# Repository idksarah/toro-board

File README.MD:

# toro-board
fully custom gasket mount 60% hot swappable alice keyboard using a raspberry pi pico. <br>

<br>
made this bc alice keyboards r cool but i've already spent too much on keyboards.

## firmware
qmk firmware

## bom

| item                                                                                     | quantity | price  | description              | vendor     | link                                                                                                                   |
|------------------------------------------------------------------------------------------|----------|--------|--------------------------|------------|------------------------------------------------------------------------------------------------------------------------|
| plate                                                                                    | 1 pc     | 3.44   | 3d-printed acrylic plate            | jlccnc     | —                                                                                                                      |
| pcb                                                                                      | 5 pc     | 21.60  | pcb                      | jlcpcb     | —                                                                                                                      |
| case bottom                                                                              | 1 pc     | 28.34  | 3d-printed acrylic bottom case              | jlccnc     | —                                                                                                                      |
| case top                                                                                 | 1 pc     | 9.35   | 3d-printed acrylic top case                 | jlccnc     | —                                                                                                                      |
| [163 keys british racing green keyboard keycaps](https://www.aliexpress.us/item/3256807785511869.html) | 163 pc   | 16.66  | keycaps                  | aliexpress | [link](https://www.aliexpress.us/item/3256807785511869.html)                                                           |
| [gateron ef curry switch 50g 5pin smd mx switch](https://www.aliexpress.us/item/3256805933064484.html) | 70 pc    | 26.69   | ef curry switches        | aliexpress | [link](https://www.aliexpress.us/item/3256805933064484.html)                                                           |
| [coiled keyboard cable type c to usb-a](https://www.aliexpress.us/item/3256808312113111.html) | 1 pc     | 7.00   | usb c to usb a cable     | aliexpress | [link](https://www.aliexpress.us/item/3256808312113111.html)                                                           |
| [70pcs kailh hot-swappable pcb socket hot plug](https://www.aliexpress.us/item/3256807039037559.html) | 70 pc    | 3.73   | kailh hot swap sockets   | aliexpress | [link](https://www.aliexpress.us/item/3256807039037559.html)                                                           |
| [15pcs gasket cotton strip](https://www.aliexpress.us/item/3256804985438216.html)        | 15 pc    | 3.74   | gasket for gasket mount  | aliexpress | [link](https://www.aliexpress.us/item/3256804985438216.html)                                                           |
| [switch puller tool](https://www.aliexpress.us/item/3256808571143767.html)               | —        | 3.92   | switch puller            | aliexpress | [link](https://www.aliexpress.us/item/3256808571143767.html)                                                           |
| shipping (jlcpcb)                                                                        | —        | 20.00  |                          | jlcpcb     | —                                                                                                                      |

---

### subtotals

- **jlcpcb total**: 21.60 (pcb) + 20.00 (shipping) → **$41.60**
- **aliexpress total**: 16.66 + 26.69 + 7.00 + 3.73 + 3.74 + 3.92 → **$61.74**
- **jlccnc total**: 3.44 + 28.34 + 9.35 → **$41.13**

---

### total: **$116.61**

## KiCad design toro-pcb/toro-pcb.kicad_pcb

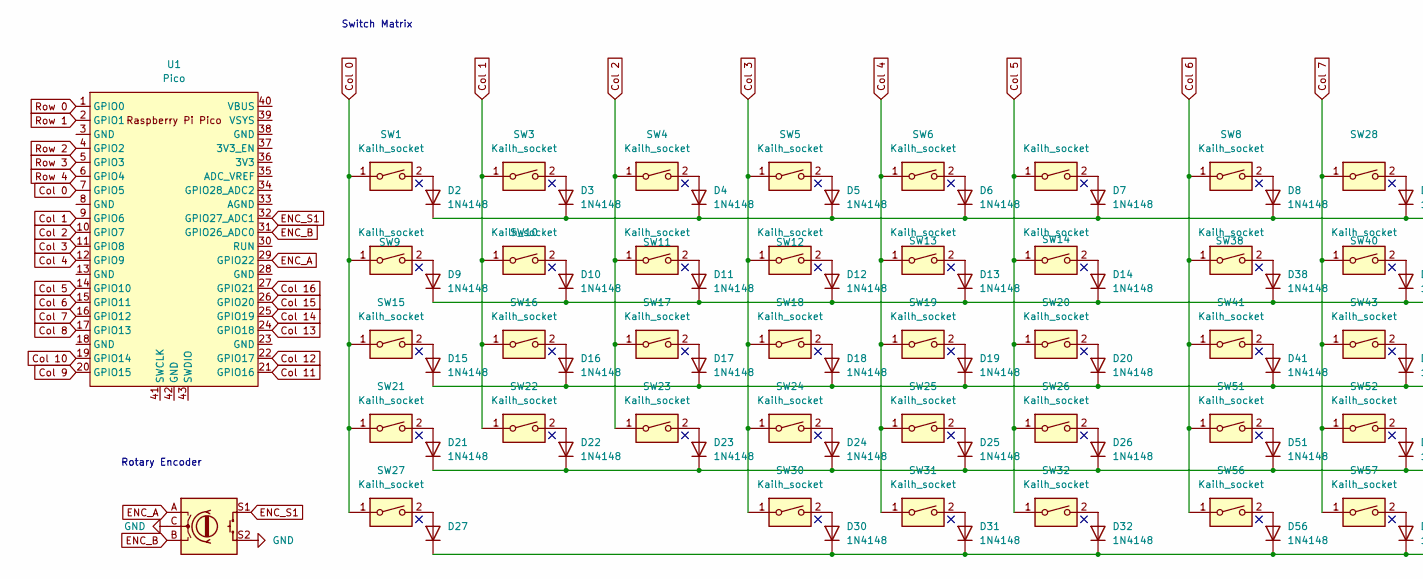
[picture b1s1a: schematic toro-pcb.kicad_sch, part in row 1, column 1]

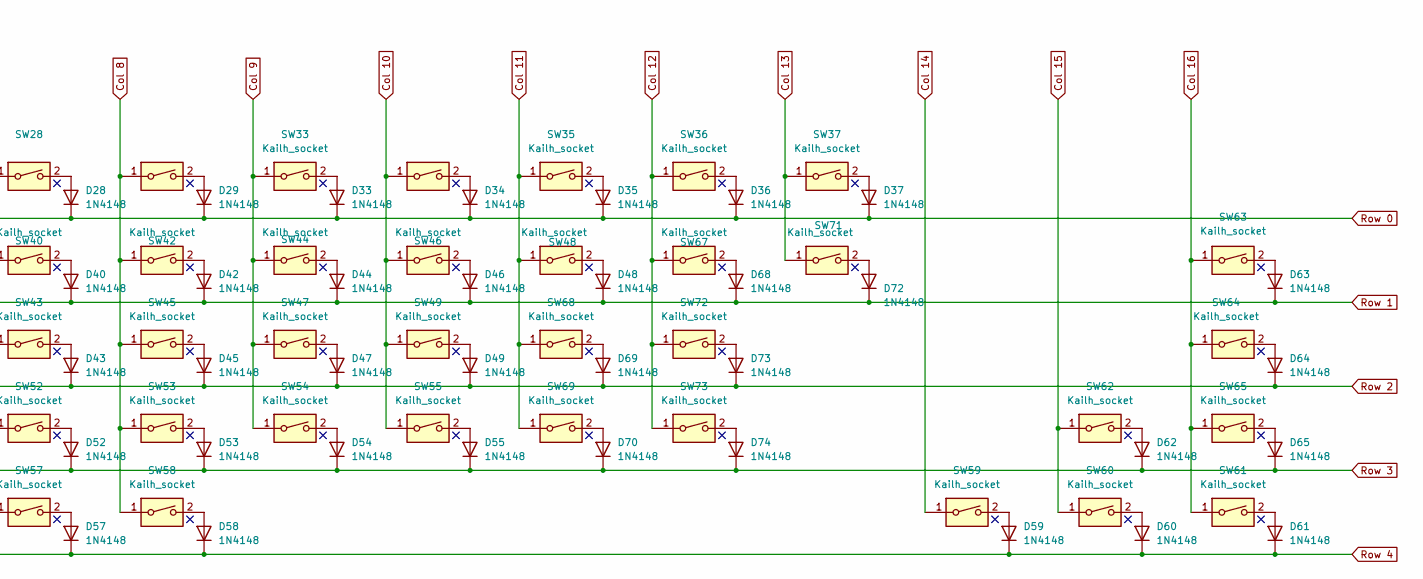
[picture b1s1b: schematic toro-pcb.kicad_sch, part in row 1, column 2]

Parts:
D2, D3, D4, D5, D6, D7, D8, D9, D10, D11, D12, D13, D14, D15, D16, D17, D18, D19, D20, D21, D22, D23, D24, D25, D26, D27, D28, D29, D30, D31, D32, D33, D34, D35, D36, D37, D38, D40, D41, D42, D43, D44, D45, D46, D47, D48, D49, D51, D52, D53, D54, D55, D56, D57, D58, D59, D60, D61, D62, D63, D64, D65, D68, D69, D70, D72, D73, D74: 1N4148; D_DO-35_SOD27_P7.62mm_Horizontal
SW1, SW3, SW4, SW5, SW6, SW7, SW8, SW9, SW10, SW11, SW12, SW13, SW14, SW15, SW16, SW17, SW18, SW19, SW20, SW21, SW22, SW23, SW24, SW25, SW26, SW27, SW28, SW29, SW30, SW31, SW32, SW33, SW34, SW35, SW36, SW37, SW38, SW40, SW41, SW42, SW43, SW44, SW45, SW46, SW47, SW48, SW49, SW51, SW52, SW53, SW54, SW55, SW56, SW57, SW58, SW59, SW60, SW61, SW62, SW63, SW64, SW65, SW67, SW68, SW69, SW71, SW72, SW73: Kailh_socket; Kailh_socket_MX
SW2: RotaryEncoder_Switch; RotaryEncoder_Alps_EC12E-Switch_Vertical_H20mm
U1: Pico; RPi_Pico_SMD_TH

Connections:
Col 1: SW3.1, SW10.1, SW16.1, SW22.1, U1.9 (GPIO6)
Col 2: SW4.1, SW11.1, SW17.1, SW23.1, U1.10 (GPIO7)
Col 3: SW5.1, SW12.1, SW18.1, SW24.1, SW30.1, U1.11 (GPIO8)
Col 4: SW6.1, SW13.1, SW19.1, SW25.1, SW31.1, U1.12 (GPIO9)
Col 6: SW8.1, SW38.1, SW41.1, SW51.1, SW56.1, U1.15 (GPIO11)
Col 7: SW28.1, SW40.1, SW43.1, SW52.1, SW57.1, U1.16 (GPIO12)
Col 8: SW29.1, SW42.1, SW45.1, SW53.1, SW58.1, U1.17 (GPIO13)
Col 9: SW33.1, SW44.1, SW47.1, SW54.1, U1.20 (GPIO15); also elsewhere on the board
Col 10: SW34.1, SW46.1, SW49.1, SW55.1, U1.19 (GPIO14)
Col 11: SW35.1, SW48.1, SW68.1, SW69.1, U1.21 (GPIO16)
Col 12: SW36.1, SW67.1, SW72.1, SW73.1, U1.22 (GPIO17)
Col 13: SW37.1, SW71.1, U1.24 (GPIO18)
Col 14: SW59.1, U1.25 (GPIO19)
Col 15: SW60.1, SW62.1, U1.26 (GPIO20)
Col 16: SW61.1, SW63.1, SW64.1, SW65.1, U1.27 (GPIO21)
ENC_A: SW2.A, U1.29 (GPIO22)
ENC_B: SW2.B, U1.31 (GPIO26_ADC0)
ENC_S1: SW2.S1, U1.32 (GPIO27_ADC1)
GND: SW2.C, SW2.S2
LEDS: U1.34 (GPIO28_ADC2)
unnamed: D2.2 (A), SW1.2
unnamed: D3.2 (A), SW3.2
unnamed: D4.2 (A), SW4.2
unnamed: D5.2 (A), SW5.2
unnamed: D6.2 (A), SW6.2
unnamed: D7.2 (A), SW7.2
unnamed: D8.2 (A), SW8.2
unnamed: D9.2 (A), SW9.2
unnamed: D10.2 (A), SW10.2
unnamed: D11.2 (A), SW11.2
unnamed: D12.2 (A), SW12.2
unnamed: D13.2 (A), SW13.2
unnamed: D17.2 (A), SW17.2
unnamed: D18.2 (A), SW18.2
unnamed: D19.2 (A), SW19.2
unnamed: D20.2 (A), SW20.2
unnamed: D21.2 (A), SW21.2
unnamed: D22.2 (A), SW22.2
unnamed: D23.2 (A), SW23.2
unnamed: D24.2 (A), SW24.2
unnamed: D25.2 (A), SW25.2
unnamed: D26.2 (A), SW26.2
unnamed: D27.2 (A), SW27.2
unnamed: D28.2 (A), SW28.2
unnamed: D29.2 (A), SW29.2
unnamed: D30.2 (A), SW30.2
unnamed: D31.2 (A), SW31.2
unnamed: D33.2 (A), SW33.2
unnamed: D34.2 (A), SW34.2
unnamed: D35.2 (A), SW35.2
unnamed: D36.2 (A), SW36.2
unnamed: D37.2 (A), SW37.2
unnamed: D38.2 (A), SW38.2
unnamed: D40.2 (A), SW40.2
unnamed: D41.2 (A), SW41.2
unnamed: D42.2 (A), SW42.2
unnamed: D43.2 (A), SW43.2
unnamed: D44.2 (A), SW44.2
unnamed: D45.2 (A), SW45.2
unnamed: D46.2 (A), SW46.2
unnamed 60: D47.2 (A), SW47.2; also elsewhere on the board
unnamed: D48.2 (A), SW48.2
unnamed: D49.2 (A), SW49.2
unnamed: D51.2 (A), SW51.2
unnamed: D52.2 (A), SW52.2
unnamed: D53.2 (A), SW53.2
unnamed: D54.2 (A), SW54.2
unnamed: D55.2 (A), SW55.2
unnamed: D56.2 (A), SW56.2
unnamed: D57.2 (A), SW57.2
unnamed: D58.2 (A), SW58.2
unnamed: D59.2 (A), SW59.2
unnamed: D60.2 (A), SW60.2
unnamed: D61.2 (A), SW61.2
unnamed: D62.2 (A), SW62.2
unnamed: D63.2 (A), SW63.2
unnamed: D64.2 (A), SW64.2
unnamed: D65.2 (A), SW65.2
unnamed: D68.2 (A), SW67.2
unnamed: D69.2 (A), SW68.2
unnamed: D70.2 (A), SW69.2
unnamed: D72.2 (A), SW71.2
unnamed: D73.2 (A), SW72.2
unnamed: D74.2 (A), SW73.2
Row 0: D2.1 (K), D3.1 (K), D4.1 (K), D5.1 (K), D6.1 (K), D7.1 (K), D8.1 (K), D28.1 (K), D29.1 (K), D33.1 (K), D34.1 (K), D35.1 (K), D36.1 (K), D37.1 (K), U1.1 (GPIO0)
Row 1: D9.1 (K), D10.1 (K), D11.1 (K), D12.1 (K), D13.1 (K), D14.1 (K), D38.1 (K), D40.1 (K), D42.1 (K), D44.1 (K), D46.1 (K), D48.1 (K), D63.1 (K), D68.1 (K), D72.1 (K), U1.2 (GPIO1)
Row 3: D21.1 (K), D22.1 (K), D23.1 (K), D24.1 (K), D25.1 (K), D26.1 (K), D51.1 (K), D52.1 (K), D53.1 (K), D54.1 (K), D55.1 (K), D62.1 (K), D65.1 (K), D70.1 (K), D74.1 (K), U1.5 (GPIO3)

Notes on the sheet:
Switch Matrix
Rotary Encoder

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
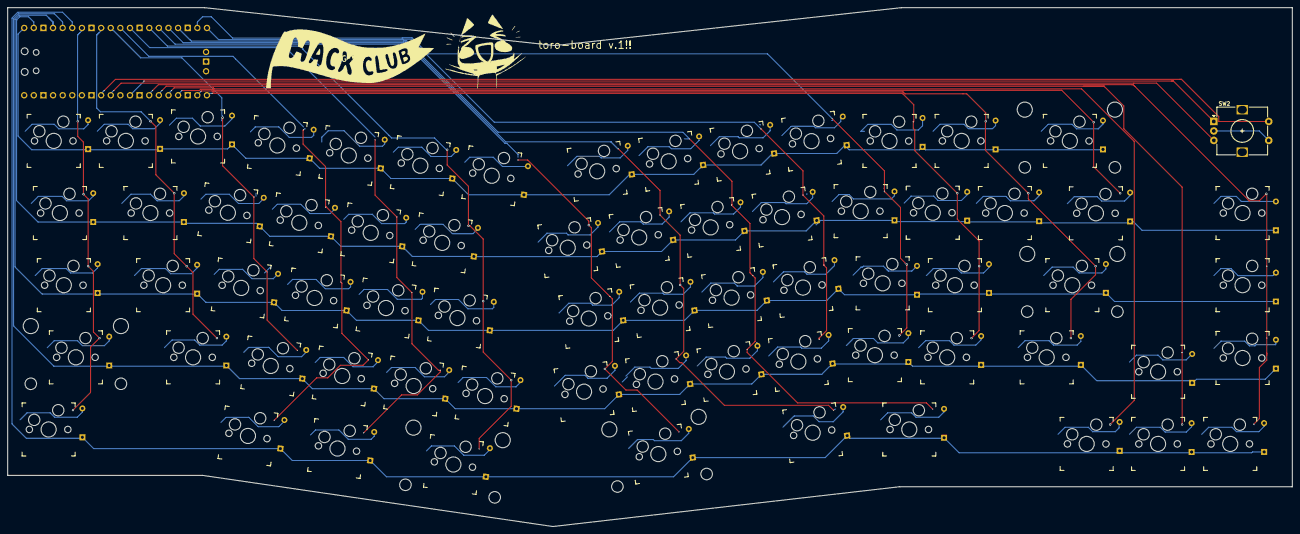
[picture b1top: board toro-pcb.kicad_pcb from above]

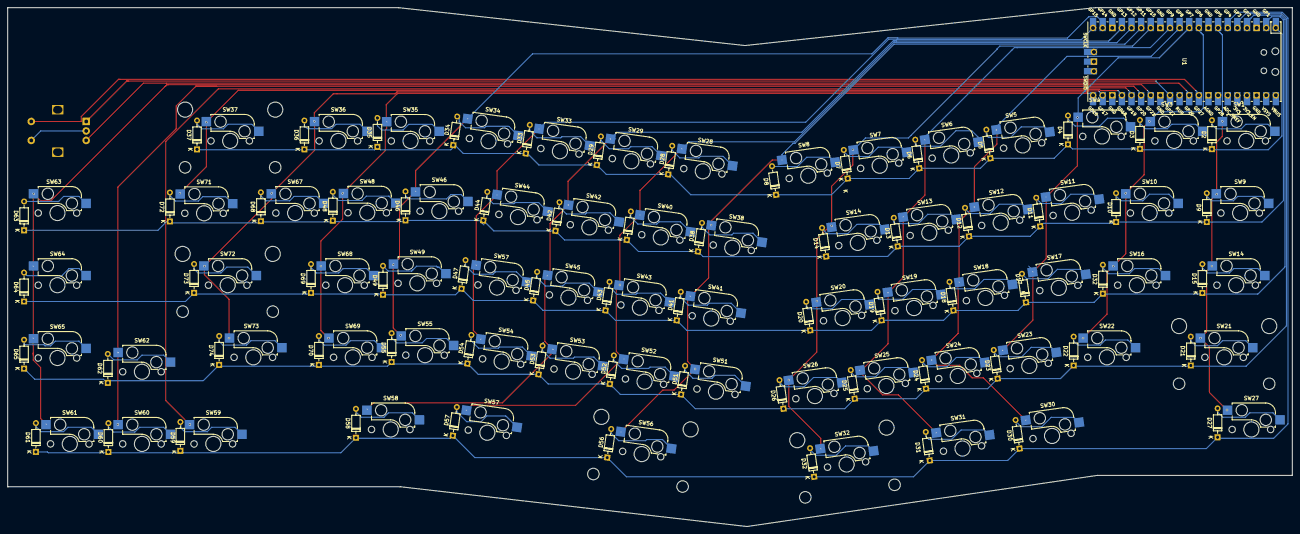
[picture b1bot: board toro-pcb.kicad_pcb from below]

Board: 2 copper layers, 339.2 x 137.0 mm, 138 parts (69 on the bottom side), 94 nets.

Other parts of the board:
D32#2: 1N4148; D_DO-35_SOD27_P7.62mm_Horizontal
SW14#2, SW57#2: Kailh_socket; Kailh_socket_MX

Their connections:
Col 9: SW57#2.1; also elsewhere on the board
unnamed 60: SW57#2.2; also elsewhere on the board

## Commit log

2025-06-05 initial
2025-06-05 alice
2025-06-05 switch layout
2025-06-05 #ididntsavemychanges. rotary encoder
2025-06-05 led strip
2025-06-06 peeceebee
2025-06-06 set distance between centers to 19.05mm + add space and footprint for stabilizers
2025-06-06 big keys
2025-06-08 spacing christ all mighty
2025-06-08 vertically aligned right side 💀
2025-06-08 move leds to back
2025-06-08 i fucked up
2025-06-08 shit
2025-06-18 iiiiiuhhhuhhh rewiring
2025-06-24 gasket mount spacing + readme
2025-06-24 links oops
2025-06-25 firmware
2025-06-25 submisiion requirements
2025-08-06 readme + kmk
